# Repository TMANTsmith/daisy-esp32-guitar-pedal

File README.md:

# Daisy Esp32 Pedal

This is a guitar pedal with the goal of combining the audio processing power of the Daisy Seed with the wifi capabilities of the Esp32C series (currently only testing the C6). This way you can fully control the guitar pedal with your phone connected by a website hosted by the esp32 and for low-latency tasks physical buttons will be on the board. This will allow for greater flexibility through the user being able to add or remove buttons by making changes to the website allowing them to have any configuration they want.

## What is used

### Hardware

The mini-pcb which includes TRS jacks for audio processing does not currently have the esp32 but processing audio with just the daisy seed is working

The full-pcb included a esp32 which is connected to the daisy seed through UART (SPI is also connected but is unused) and includes 2 TS jacks this pcb has been designed tested.

#### mini-pcb

- [x] Finished development
- [x] Passed testing

#### full-pcb

|                                 Front                                  |                                 Back                                  |
| :--------------------------------------------------------------------: | :-------------------------------------------------------------------: |
|  |  |

- [x] Finished development
- [x] Passed testing

#### seed-pedal

This will copy the new 3Seed data sheet recommended configuration for instrument level audio and will be the final version

- [ ] Finished development
- [ ] Passed testing

### Software

The project is written in rust and uses embassy as the async executor. Specifically the [daisy-embassy](https://github.com/daisy-embassy/daisy-embassy/tree/master) which has some audio stuff, like a DMA buffer, built in.

## Examples

### Fast-Fourier Transform

- This does a FFT using [microfft](https://gitlab.com/teskje/microfft-rs) but includes things like using the SDRAM on the seed as the heap, interrupts, and how to share information between executor, how to make and use buffer for audio analysis, and more.
- This can show the difference frequencies that a guitar makes when a note it played
- It also has a added mute button

### Looper (work in progress)

- This works like a looper pedal with multiple channels to record different tracks and will be compatible physically so that you can send input to the controller using the website or a physical button
- This uses bit-manipulation to ensure that the commands send and received are compact even if the command library is expanded

## Future Ideas

### Compatibility With Tonebridge

- There are already projects that work with it and all there seems to be is a emulated microphone and speaker which the esp32 may be able to

### Ability to chain custom effects

### More effects

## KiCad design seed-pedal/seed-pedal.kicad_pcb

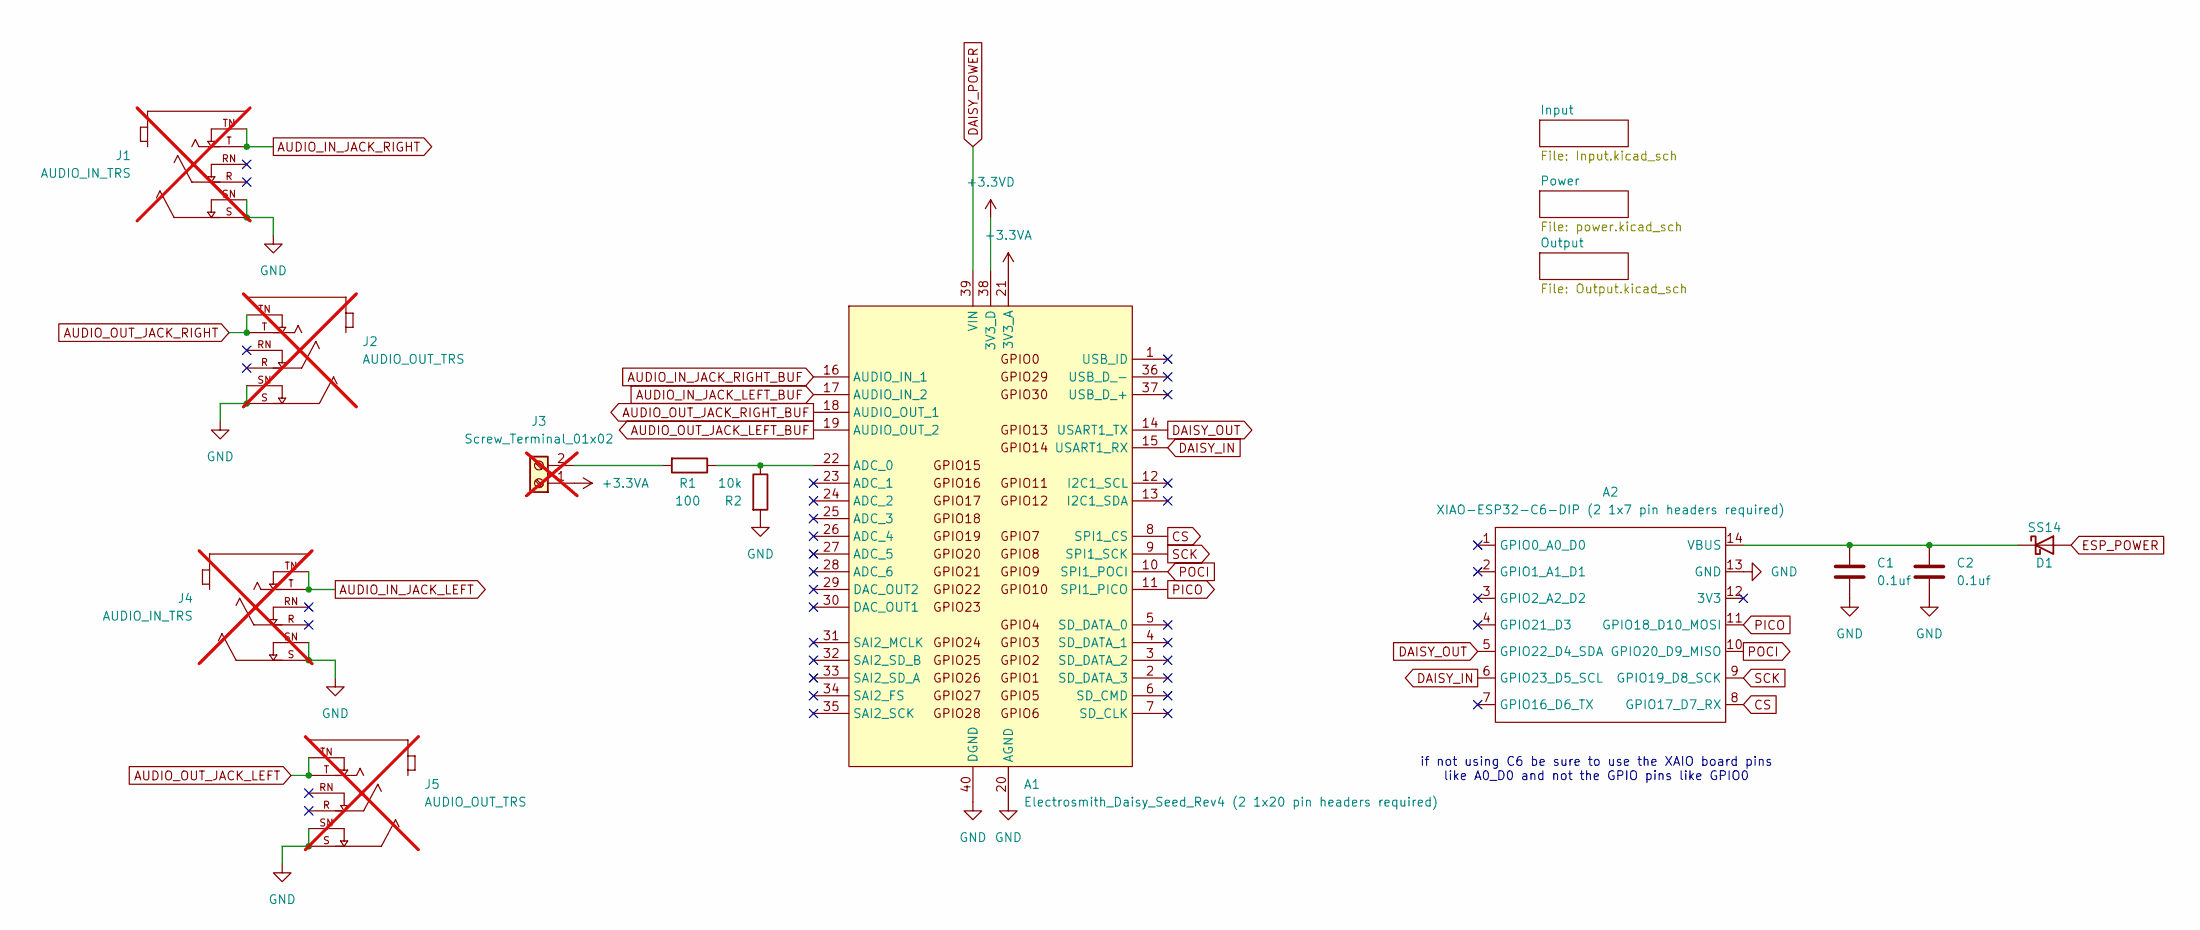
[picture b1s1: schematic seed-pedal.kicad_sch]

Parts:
A1: Electrosmith_Daisy_Seed_Rev4 (2 1x20 pin headers 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; Electrosmith_Daisy_Seed; MPN C50984
A2: XIAO-ESP32-C6-DIP (2 1x7 pin headers required); XIAO-ESP32-C6-DIP; MPN C5371993
C1, C2: 0.1uf; C_0603_1608Metric; MPN C49678
D1: SS14; D_SMA; MPN C2480
J1, J4: AUDIO_IN_TRS; Jack_6.35mm_Neutrik_NMJ6HCD3_Horizontal; PARTREV 26.02.2021; not fitted
J2, J5: AUDIO_OUT_TRS; Jack_6.35mm_Neutrik_NMJ6HCD3_Horizontal; PARTREV 26.02.2021; not fitted
J3: Screw_Terminal_01x02; TerminalBlock_Xinya_XY308-2.54-2P_1x02_P2.54mm_Horizontal; MPN C8465; not fitted
R1: 100; R_0603_1608Metric; MPN C22775
R2: 10k; R_0603_1608Metric; MPN C25804

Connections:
+3.3VA: A1.21 (3V3_A), J3.1
+3.3VD: A1.38 (3V3_D)
AUDIO_IN_JACK_LEFT: J4.T, J4.TN; also elsewhere on the board
AUDIO_IN_JACK_LEFT_BUF: A1.17 (AUDIO_IN_2); also elsewhere on the board
AUDIO_IN_JACK_RIGHT: J1.T, J1.TN; also elsewhere on the board
AUDIO_IN_JACK_RIGHT_BUF: A1.16 (AUDIO_IN_1); also elsewhere on the board
AUDIO_OUT_JACK_LEFT: J5.T, J5.TN; also elsewhere on the board
AUDIO_OUT_JACK_LEFT_BUF: A1.19 (AUDIO_OUT_2); also elsewhere on the board
AUDIO_OUT_JACK_RIGHT: J2.T, J2.TN; also elsewhere on the board
AUDIO_OUT_JACK_RIGHT_BUF: A1.18 (AUDIO_OUT_1); also elsewhere on the board
CS: A1.8 (SPI1_CS), A2.8 (GPIO17_D7_RX)
DAISY_IN: A1.15 (USART1_RX), A2.6 (GPIO23_D5_SCL)
DAISY_OUT: A1.14 (USART1_TX), A2.5 (GPIO22_D4_SDA)
DAISY_POWER: A1.39 (VIN); also elsewhere on the board
ESP_POWER: D1.2 (A); also elsewhere on the board
GND: A1.20 (AGND), A1.40 (DGND), A2.13 (GND), C1.2, C2.2, J1.S, J1.SN, J2.S, J2.SN, J4.S, J4.SN, J5.S, J5.SN, R2.2; also elsewhere on the board
unnamed: A1.22 (ADC_0), R1.1, R2.1
unnamed: A2.14 (VBUS), C1.1, C2.1, D1.1 (K)
unnamed: J3.2, R1.2
PICO: A1.11 (SPI1_PICO), A2.11 (GPIO18_D10_MOSI)
POCI: A1.10 (SPI1_POCI), A2.10 (GPIO20_D9_MISO)
SCK: A1.9 (SPI1_SCK), A2.9 (GPIO19_D8_SCK)

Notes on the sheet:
if not using C6 be sure to use the XAIO board pins like A0_D0 and not the GPIO pins like GPIO0

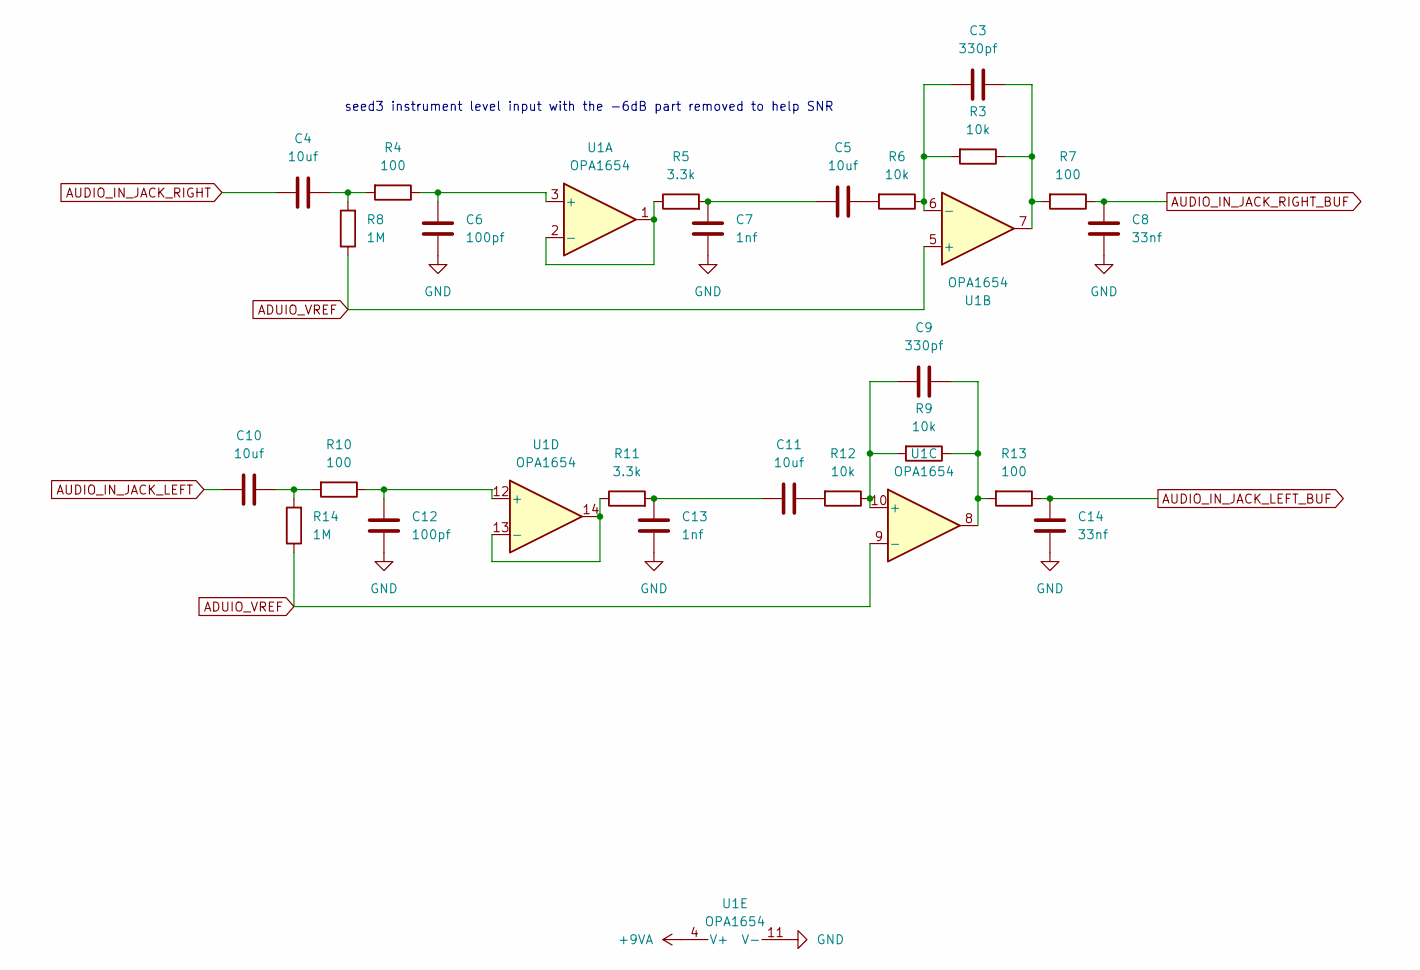
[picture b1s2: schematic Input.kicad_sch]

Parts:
C3, C9: 330pf; C_0603_1608Metric; MPN C1664
C4, C5, C10, C11: 10uf; C_0603_1608Metric; MPN C96446
C6, C12: 100pf; C_0603_1608Metric; MPN C14858
C7, C13: 1nf; C_0603_1608Metric; MPN C1588
C8, C14: 33nf; C_0603_1608Metric; MPN C21117
R3, R6, R9, R12: 10k; R_0603_1608Metric; MPN C25804
R4, R7, R10, R13: 100; R_0603_1608Metric; MPN C22775
R5, R11: 3.3k; R_0603_1608Metric; MPN C22978
R8, R14: 1M; R_0603_1608Metric; MPN C22935
U1: OPA1654; SOIC-14_3.9x8.7mm_P1.27mm; MPN C30026

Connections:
+9VA: U1.4 (V+); also elsewhere on the board
ADUIO_VREF: R8.1, R14.1, U1.5 (+), U1.9 (-); also elsewhere on the board
AUDIO_IN_JACK_LEFT: C10.1; also elsewhere on the board
AUDIO_IN_JACK_LEFT_BUF: C14.1, R13.1; also elsewhere on the board
AUDIO_IN_JACK_RIGHT: C4.1; also elsewhere on the board
AUDIO_IN_JACK_RIGHT_BUF: C8.1, R7.1; also elsewhere on the board
GND: C6.2, C7.2, C8.2, C12.2, C13.2, C14.2, U1.11 (V-); also elsewhere on the board
unnamed: C3.2, R3.1, R7.2, U1.7
unnamed: C4.2, R4.2, R8.2
unnamed: C5.1, C7.1, R5.2
unnamed: C5.2, R6.2
unnamed: C9.2, R9.1, R13.2, U1.8
unnamed: C10.2, R10.2, R14.2
unnamed: C11.1, C13.1, R11.2
unnamed: C11.2, R12.2
unnamed: C6.1, R4.1, U1.3 (+)
unnamed: R5.1, U1.1, U1.2 (-)
unnamed: C3.1, R3.2, R6.1, U1.6 (-)
unnamed: C9.1, R9.2, R12.1, U1.10 (+)
unnamed: C12.1, R10.1, U1.12 (+)
unnamed: R11.1, U1.13 (-), U1.14

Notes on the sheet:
seed3 instrument level input with the -6dB part removed to help SNR

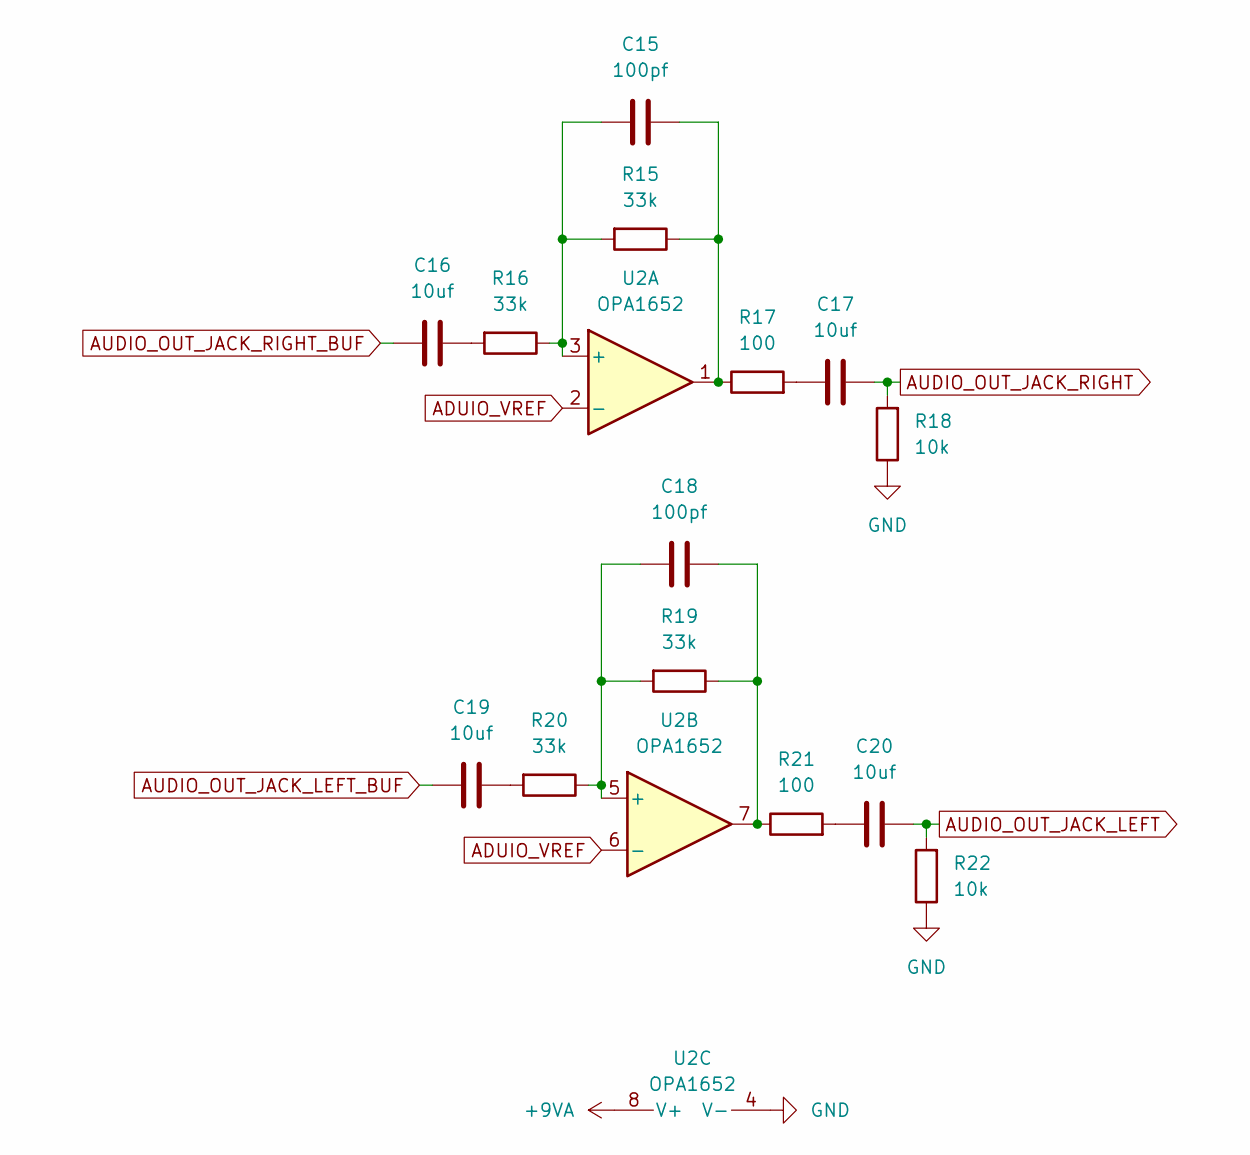
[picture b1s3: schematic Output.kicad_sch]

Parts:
C15, C18: 100pf; C_0603_1608Metric; MPN C14858
C16, C17, C19, C20: 10uf; C_0603_1608Metric; MPN C96446
R15, R16, R19, R20: 33k; R_0603_1608Metric; MPN C4216
R17, R21: 100; R_0603_1608Metric; MPN C22775
R18, R22: 10k; R_0603_1608Metric; MPN C25804
U2: OPA1652; SOIC-8_3.9x4.9mm_P1.27mm

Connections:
+9VA: U2.8 (V+); also elsewhere on the board
ADUIO_VREF: U2.2 (-), U2.6 (-); also elsewhere on the board
AUDIO_OUT_JACK_LEFT: C20.2, R22.2; also elsewhere on the board
AUDIO_OUT_JACK_LEFT_BUF: C19.1; also elsewhere on the board
AUDIO_OUT_JACK_RIGHT: C17.2, R18.2; also elsewhere on the board
AUDIO_OUT_JACK_RIGHT_BUF: C16.1; also elsewhere on the board
GND: R18.1, R22.1, U2.4 (V-); also elsewhere on the board
unnamed: C15.2, R15.1, R17.1, U2.1
unnamed: C16.2, R16.2
unnamed: C17.1, R17.2
unnamed: C18.2, R19.1, R21.1, U2.7
unnamed: C19.2, R20.2
unnamed: C20.1, R21.2
unnamed: C15.1, R15.2, R16.1, U2.3 (+)
unnamed: C18.1, R19.2, R20.1, U2.5 (+)

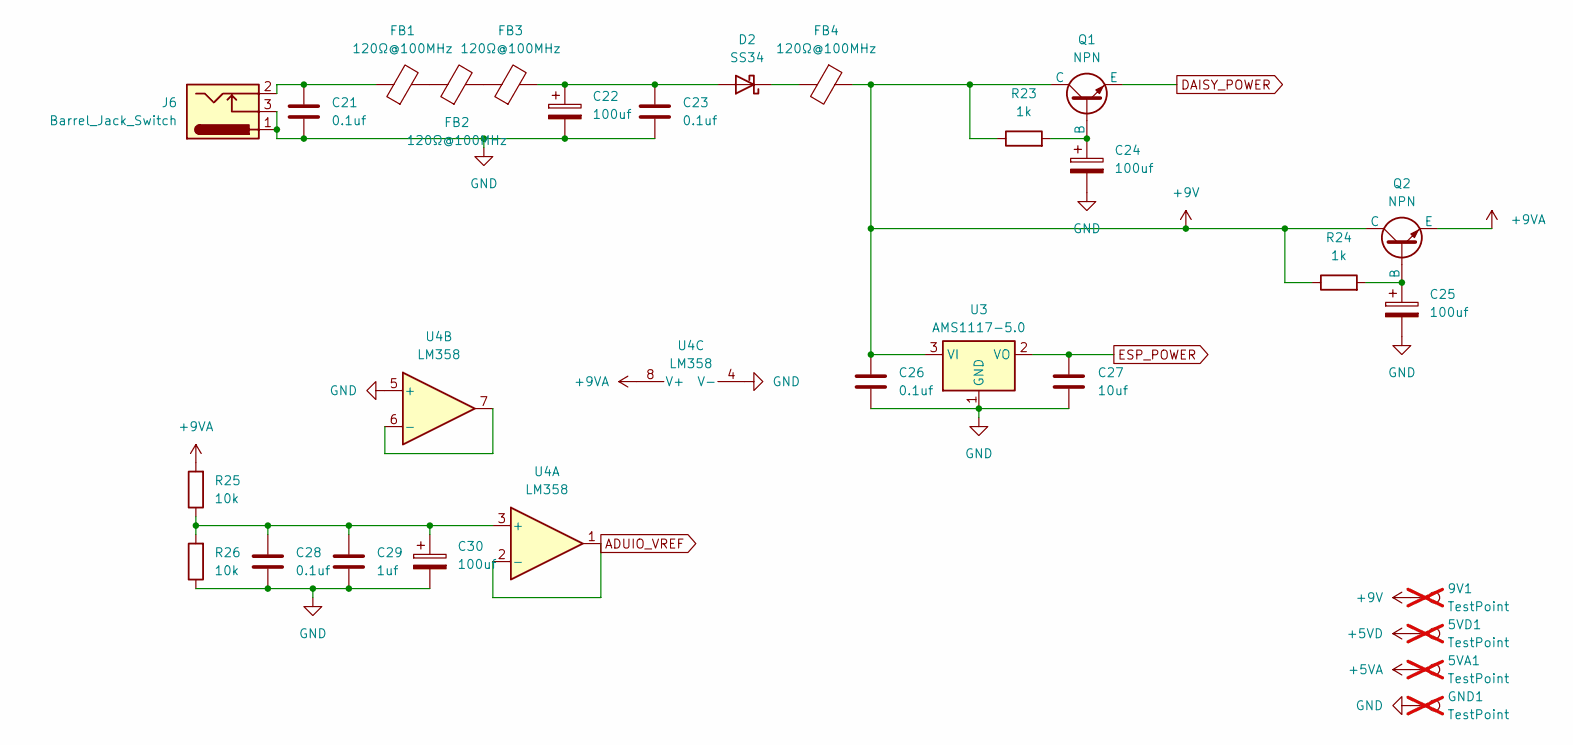
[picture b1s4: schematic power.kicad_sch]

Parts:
5VA1, 5VD1, 9V1: TestPoint; PinHeader_1x01_P2.54mm_Vertical; not fitted
C21, C23, C26, C28: 0.1uf; C_0805_2012Metric; MPN C49678
C22, C24, C25, C30: 100uf; CP_Radial_D8.0mm_P3.50mm; MPN C5113358
C27: 10uf; C_0805_2012Metric; MPN C15850
C29: 1uf; C_0805_2012Metric; MPN C28323
D2: SS34; D_SMA
FB1, FB2, FB3, FB4: 120Ω@100MHz; R_0603_1608Metric; MPN BLM18PG121SN1D
GND1: TestPoint; PinHeader_1x01_P2.54mm_Vertical; not fitted
J6: Barrel_Jack_Switch; BarrelJack_Horizontal; MPN C16214
Q1, Q2: NPN; SOT-89-3; MPN C41375136
R23, R24: 1k; R_0603_1608Metric; MPN C21190
R25, R26: 10k; R_0603_1608Metric; MPN C25804
U3: AMS1117-5.0; SOT-223-3_TabPin2
U4: LM358; SOIC-8_3.9x4.9mm_P1.27mm

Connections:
+9V: 9V1.1, C26.1, FB4.1, Q1.1 (C), Q2.1 (C), R23.1, R24.1, U3.3 (VI)
+9VA: Q2.3 (E), R25.2, U4.8 (V+); also elsewhere on the board
ADUIO_VREF: U4.1, U4.2 (-); also elsewhere on the board
DAISY_POWER: Q1.3 (E); also elsewhere on the board
ESP_POWER: C27.2, U3.2 (VO); also elsewhere on the board
GND: C21.2, C22.2, C23.2, C24.2, C25.2, C26.2, C27.1, C28.2, C29.2, C30.2, GND1.1 (1_1), J6.1, J6.3, R26.1, U3.1 (GND), U4.4 (V-), U4.5 (+); also elsewhere on the board
unnamed: C21.1, FB1.1, J6.2
unnamed: C22.1, C23.1, D2.2 (A), FB3.2
unnamed: D2.1 (K), FB4.2
unnamed: FB1.2, FB2.1
unnamed: FB2.2, FB3.1
unnamed: C24.1, Q1.2 (B), R23.2
unnamed: C25.1, Q2.2 (B), R24.2
unnamed: C28.1, C29.1, C30.1, R25.1, R26.2, U4.3 (+)
unnamed: U4.6 (-), U4.7

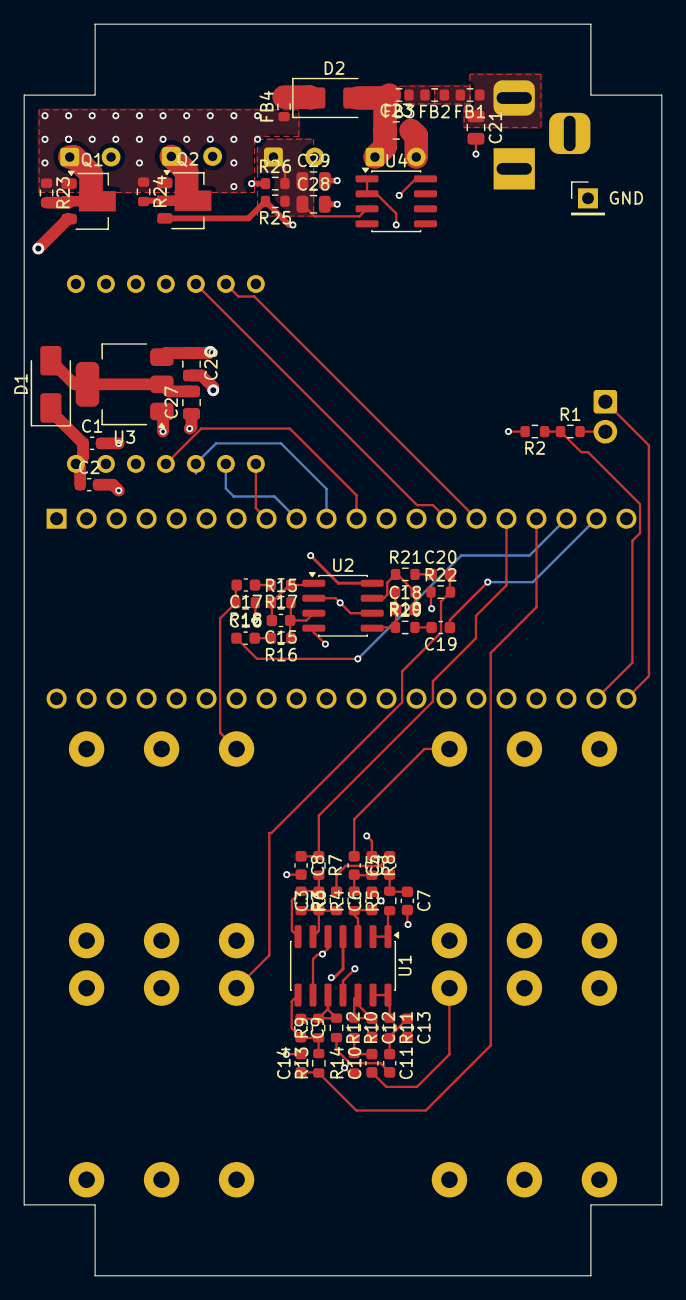
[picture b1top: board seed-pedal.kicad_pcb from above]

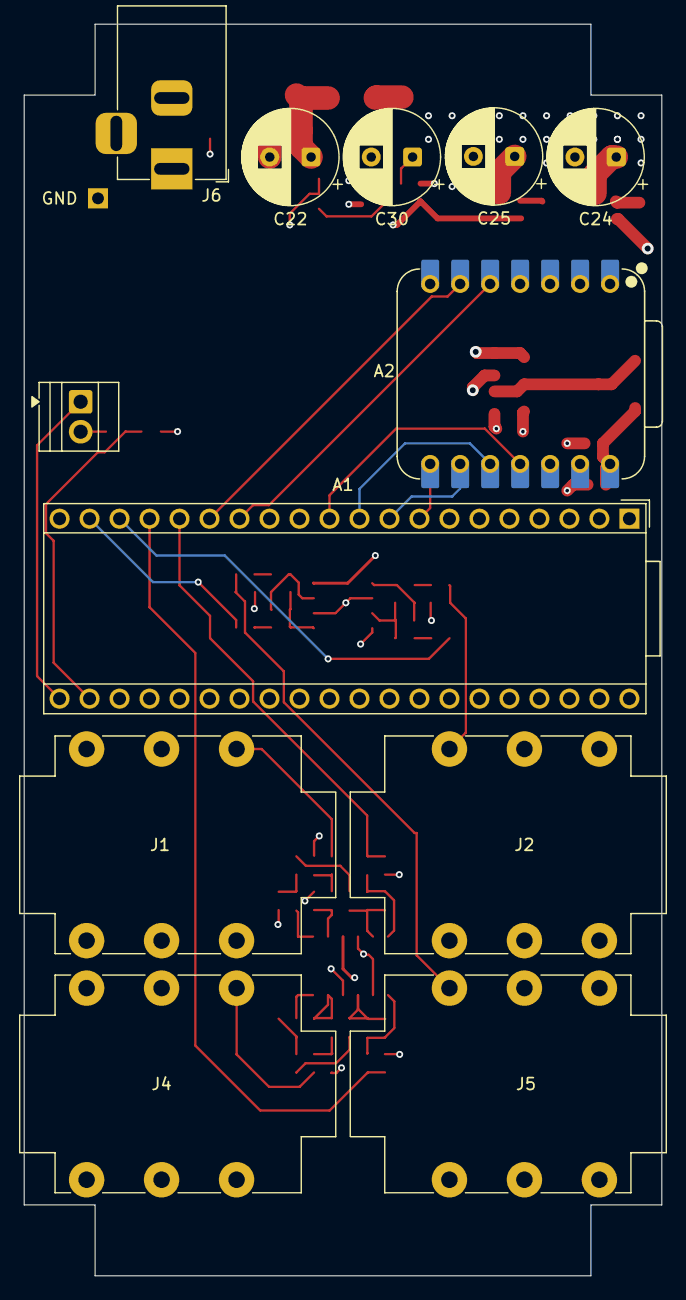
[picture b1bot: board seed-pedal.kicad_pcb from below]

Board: 4 copper layers, 54.0 x 106.0 mm, 77 parts (12 on the bottom side), 55 nets.

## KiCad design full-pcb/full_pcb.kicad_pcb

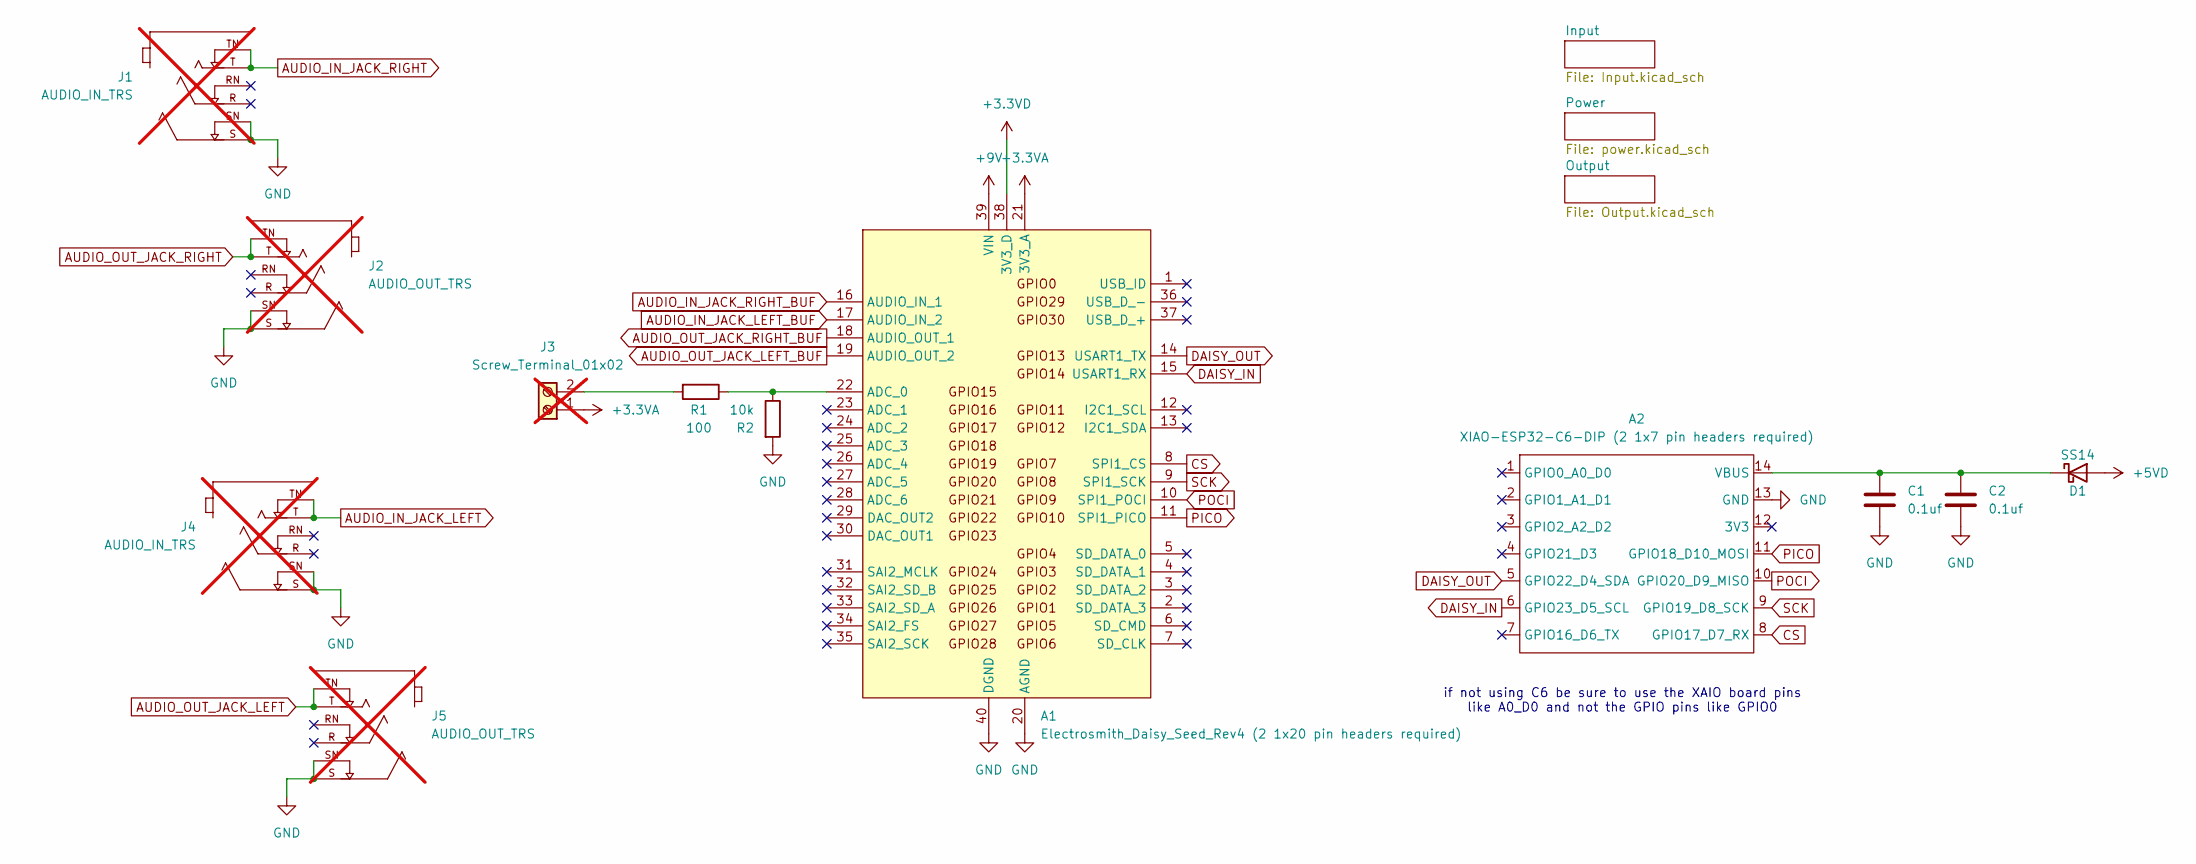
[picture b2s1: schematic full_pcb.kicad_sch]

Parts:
A1: Electrosmith_Daisy_Seed_Rev4 (2 1x20 pin headers 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; Electrosmith_Daisy_Seed; MPN C50984
A2: XIAO-ESP32-C6-DIP (2 1x7 pin headers required); XIAO-ESP32-C6-DIP; MPN C5371993
C1, C2: 0.1uf; C_0805_2012Metric; MPN C49678
D1: SS14; D_SMA; MPN C2480
J1, J4: AUDIO_IN_TRS; Jack_6.35mm_Neutrik_NMJ6HCD3_Horizontal; PARTREV 26.02.2021; not fitted
J2, J5: AUDIO_OUT_TRS; Jack_6.35mm_Neutrik_NMJ6HCD3_Horizontal; PARTREV 26.02.2021; not fitted
J3: Screw_Terminal_01x02; TerminalBlock_Xinya_XY308-2.54-2P_1x02_P2.54mm_Horizontal; MPN C8465; not fitted
R1: 100; R_0603_1608Metric; MPN C22775
R2: 10k; R_0603_1608Metric; MPN C25804

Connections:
+3.3VA: A1.21 (3V3_A), J3.1
+3.3VD: A1.38 (3V3_D)
+5VD: D1.2 (A); also elsewhere on the board
+9V: A1.39 (VIN); also elsewhere on the board
AUDIO_IN_JACK_LEFT: J4.T, J4.TN; also elsewhere on the board
AUDIO_IN_JACK_LEFT_BUF: A1.17 (AUDIO_IN_2); also elsewhere on the board
AUDIO_IN_JACK_RIGHT: J1.T, J1.TN; also elsewhere on the board
AUDIO_IN_JACK_RIGHT_BUF: A1.16 (AUDIO_IN_1); also elsewhere on the board
AUDIO_OUT_JACK_LEFT: J5.T, J5.TN; also elsewhere on the board
AUDIO_OUT_JACK_LEFT_BUF: A1.19 (AUDIO_OUT_2); also elsewhere on the board
AUDIO_OUT_JACK_RIGHT: J2.T, J2.TN; also elsewhere on the board
AUDIO_OUT_JACK_RIGHT_BUF: A1.18 (AUDIO_OUT_1); also elsewhere on the board
CS: A1.8 (SPI1_CS), A2.8 (GPIO17_D7_RX)
DAISY_IN: A1.15 (USART1_RX), A2.6 (GPIO23_D5_SCL)
DAISY_OUT: A1.14 (USART1_TX), A2.5 (GPIO22_D4_SDA)
GND: A1.20 (AGND), A1.40 (DGND), A2.13 (GND), C1.2, C2.2, J1.S, J1.SN, J2.S, J2.SN, J4.S, J4.SN, J5.S, J5.SN, R2.2; also elsewhere on the board
unnamed: A1.22 (ADC_0), R1.1, R2.1
unnamed: A2.14 (VBUS), C1.1, C2.1, D1.1 (K)
unnamed: J3.2, R1.2
PICO: A1.11 (SPI1_PICO), A2.11 (GPIO18_D10_MOSI)
POCI: A1.10 (SPI1_POCI), A2.10 (GPIO20_D9_MISO)
SCK: A1.9 (SPI1_SCK), A2.9 (GPIO19_D8_SCK)

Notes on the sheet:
if not using C6 be sure to use the XAIO board pins like A0_D0 and not the GPIO pins like GPIO0

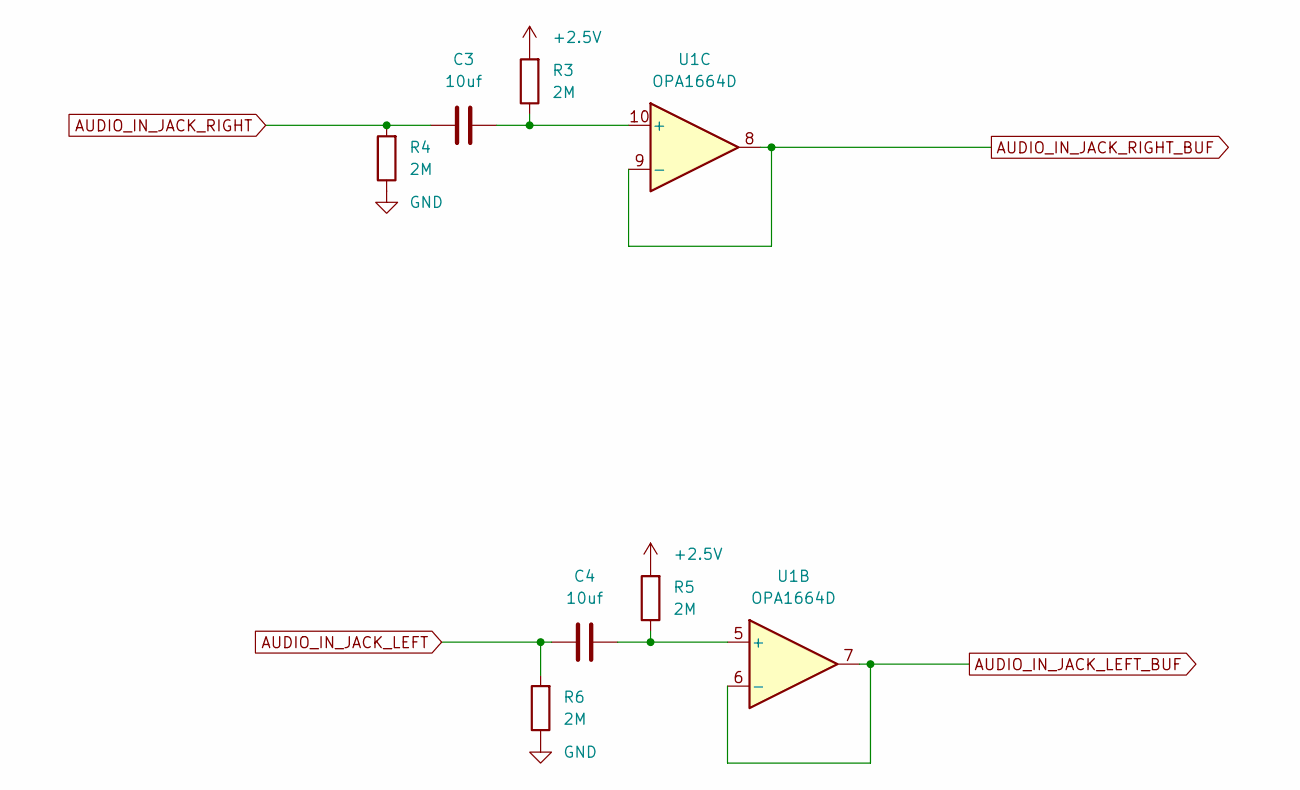
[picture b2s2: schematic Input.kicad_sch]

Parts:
C3, C4: 10uf; C_0805_2012Metric; MPN C440198
R3, R4, R5, R6: 2M; R_0603_1608Metric; MPN C22976
U1: OPA1664D; SOIC-14_3.9x8.7mm_P1.27mm; MPN C69414

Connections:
+2.5V: R3.2, R5.2; also elsewhere on the board
AUDIO_IN_JACK_LEFT: C4.1, R6.2; also elsewhere on the board
AUDIO_IN_JACK_LEFT_BUF: U1.6 (-), U1.7; also elsewhere on the board
AUDIO_IN_JACK_RIGHT: C3.1, R4.2; also elsewhere on the board
AUDIO_IN_JACK_RIGHT_BUF: U1.8, U1.9 (-); also elsewhere on the board
GND: R4.1, R6.1; also elsewhere on the board
unnamed: C4.2, R5.1, U1.5 (+)
unnamed: C3.2, R3.1, U1.10 (+)

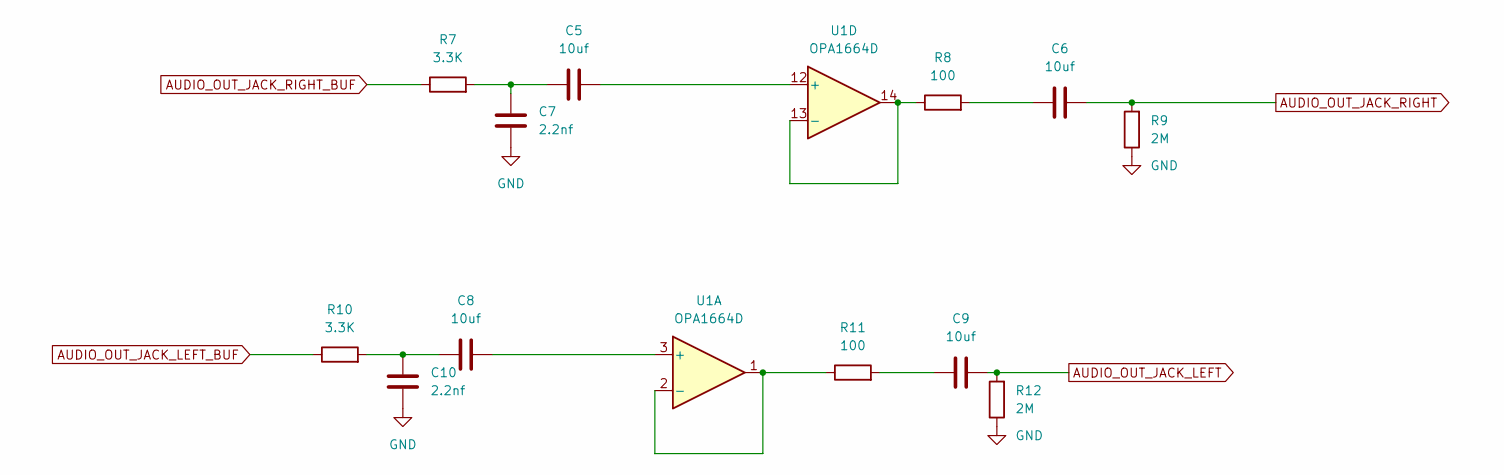
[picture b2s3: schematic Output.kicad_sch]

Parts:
C5, C6, C8, C9: 10uf; C_0805_2012Metric; MPN C440198
C7, C10: 2.2nf; C_0805_2012Metric; MPN C28260
R7, R10: 3.3K; R_0603_1608Metric; MPN C22978
R8, R11: 100; R_0603_1608Metric; MPN C22775
R9, R12: 2M; R_0603_1608Metric; MPN C22976
U1: OPA1664D; SOIC-14_3.9x8.7mm_P1.27mm; MPN C69414

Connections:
AUDIO_OUT_JACK_LEFT: C9.2, R12.2; also elsewhere on the board
AUDIO_OUT_JACK_LEFT_BUF: R10.1; also elsewhere on the board
AUDIO_OUT_JACK_RIGHT: C6.2, R9.2; also elsewhere on the board
AUDIO_OUT_JACK_RIGHT_BUF: R7.1; also elsewhere on the board
GND: C7.1, C10.1, R9.1, R12.1; also elsewhere on the board
unnamed: C5.1, C7.2, R7.2
unnamed: C6.1, R8.2
unnamed: C9.1, R11.2
unnamed: C8.1, C10.2, R10.2
unnamed: C8.2, U1.3 (+)
unnamed: R11.1, U1.1, U1.2 (-)
unnamed: C5.2, U1.12 (+)
unnamed: R8.1, U1.13 (-), U1.14

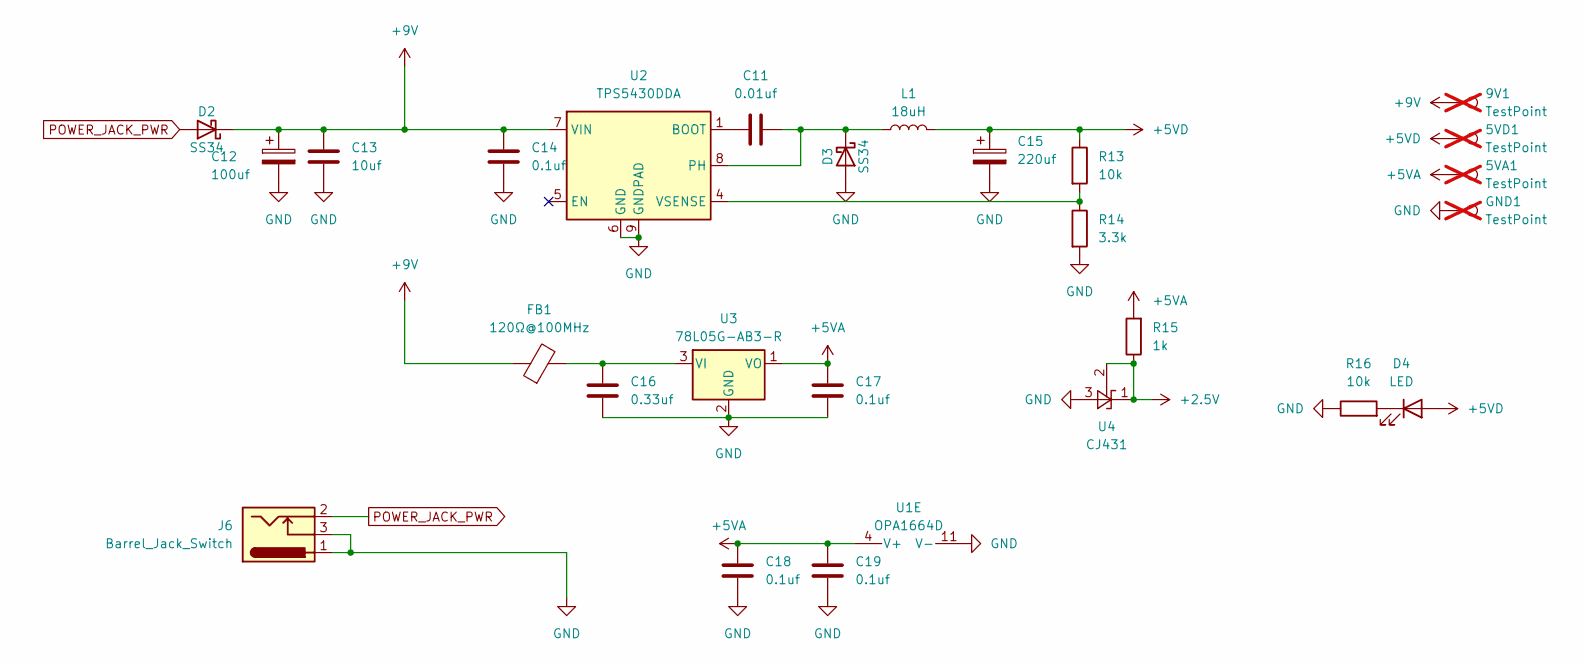
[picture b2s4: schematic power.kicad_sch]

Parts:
5VA1, 5VD1, 9V1: TestPoint; PinHeader_1x01_P2.54mm_Vertical; not fitted
C11: 0.01uf; C_0805_2012Metric; MPN C1710
C12: 100uf; CP_EIA-3528-21_Kemet-B; MPN C16133
C13: 10uf; C_0805_2012Metric; MPN C440198
C14, C17, C18, C19: 0.1uf; C_0805_2012Metric; MPN C49678
C15: 220uf; CP_EIA-7343-31_Kemet-D; MPN C242173
C16: 0.33uf; C_0805_2012Metric; MPN C1740
D2, D3: SS34; D_SMA; MPN C8678
D4: LED; LED_0805_2012Metric; MPN C2297
FB1: 120Ω@100MHz; R_0603_1608Metric; MPN C14709
GND1: TestPoint; PinHeader_1x01_P2.54mm_Vertical; not fitted
J6: Barrel_Jack_Switch; BarrelJack_Horizontal; MPN C16214
L1: 18uH; L_Changjiang_FNR8040S; MPN C168130
R13, R16: 10k; R_0603_1608Metric; MPN C25804
R14: 3.3k; R_0603_1608Metric; MPN C22978
R15: 1k; R_0603_1608Metric; MPN C21190
U1: OPA1664D; SOIC-14_3.9x8.7mm_P1.27mm; MPN C69414
U2: TPS5430DDA; TI_SO-PowerPAD-8_ThermalVias; MPN C9864
U3: 78L05G-AB3-R; SOT-89-3; MPN C71136
U4: CJ431; SOT-23-3; MPN C3113

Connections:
+2.5V: R15.1, U4.1 (FB), U4.2 (K); also elsewhere on the board
+5VA: 5VA1.1 (1_1), C17.2, C18.1, C19.1, R15.2, U1.4 (V+), U3.1 (VO)
+5VD: 5VD1.1 (1_1), C15.1, D4.2 (A), L1.2, R13.1; also elsewhere on the board
+9V: 9V1.1 (1_1), C12.1, C13.2, C14.2, D2.1 (K), FB1.1, U2.7 (VIN); also elsewhere on the board
GND: C12.2, C13.1, C14.1, C15.2, C16.1, C17.1, C18.2, C19.2, D3.2 (A), GND1.1 (1_1), J6.1, J6.3, R14.2, R16.1, U1.11 (V-), U2.6 (GND), U2.9 (GNDPAD), U3.2 (GND), U4.3 (A); also elsewhere on the board
unnamed: C11.2, D3.1 (K), L1.1, U2.8 (PH)
unnamed: D4.1 (K), R16.2
unnamed: C11.1, U2.1 (BOOT)
unnamed: R13.2, R14.1, U2.4 (VSENSE)
unnamed: C16.2, FB1.2, U3.3 (VI)
POWER_JACK_PWR: D2.2 (A), J6.2

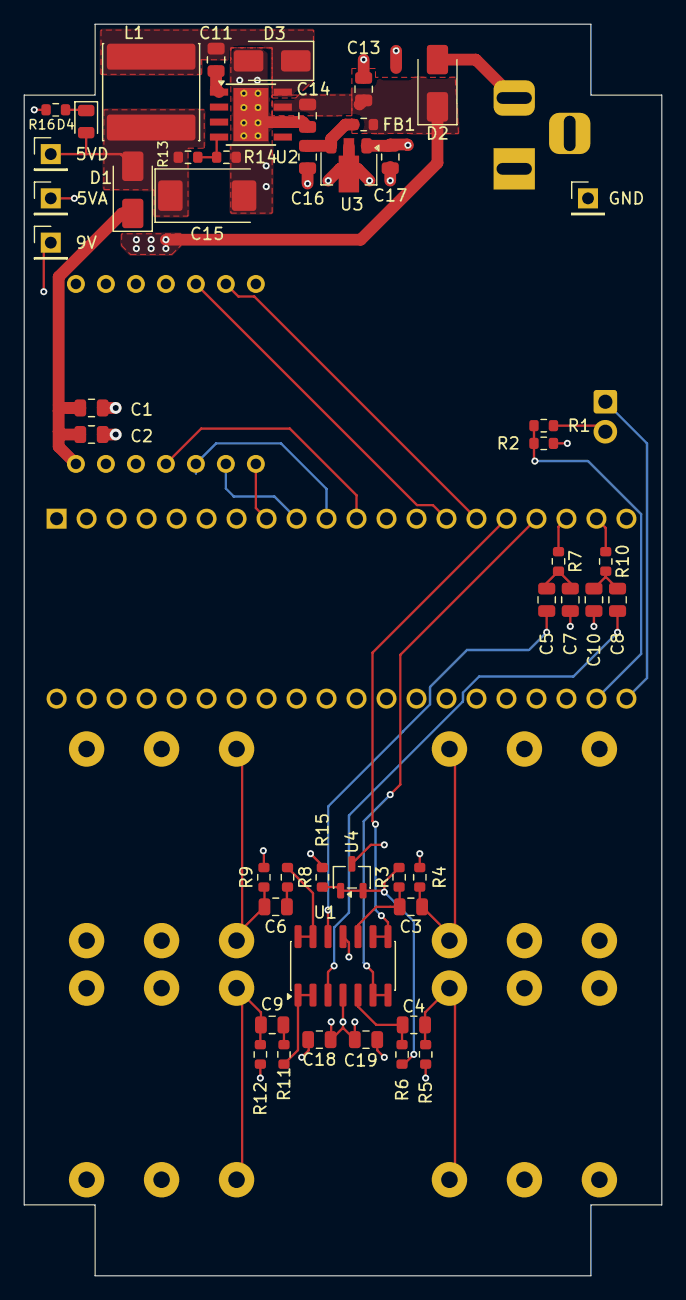
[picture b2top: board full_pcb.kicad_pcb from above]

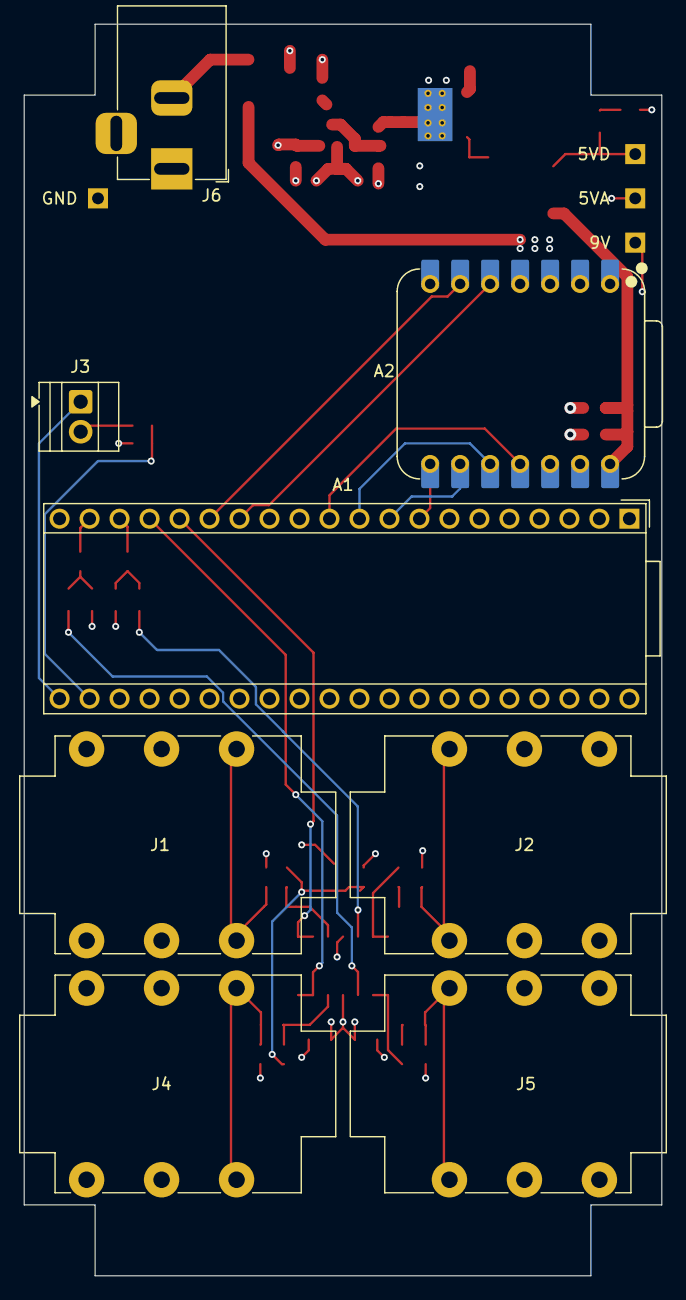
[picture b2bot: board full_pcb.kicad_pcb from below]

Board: 4 copper layers, 54.0 x 106.0 mm, 56 parts (8 on the bottom side), 39 nets.

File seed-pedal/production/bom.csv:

Designator,Footprint,Quantity,Value,LCSC Part #
"5VA1, 5VD1, 9V1, GND1",PinHeader_1x01_P2.54mm_Vertical,4,TestPoint,
A1,Electrosmith_Daisy_Seed,1,Electrosmith_Daisy_Seed_Rev4 (2 1x20 pin headers required),C50984
A2,XIAO-ESP32-C6-DIP,1,XIAO-ESP32-C6-DIP  (2 1x7 pin headers required),C5371993
"C1, C14, C17, C18, C19, C2",0805,6,0.1uf,C49678
"C10, C7",0805,2,2.2nf,C28260
C11,0805,1,0.01uf,C1710
C12,CP_EIA-3528-21_Kemet-B,1,100uf,C16133
"C13, C3, C4, C5, C6, C8, C9",0805,7,10uf,C440198
C15,CP_EIA-7343-31_Kemet-D,1,220uf,C242173
C16,0805,1,0.33uf,C1740
D1,D_SMA,1,SS14,C2480
"D2, D3",D_SMA,2,SS34,C8678
D4,0805,1,LED,C2297
FB1,0603,1,120Ω@100MHz,C14709
J6,BarrelJack_Horizontal,1,Barrel_Jack_Switch,C16214
L1,L_Changjiang_FNR8040S,1,18uH,C168130
"R1, R11, R8",0603,3,100,C22775
"R10, R14, R7",0603,3,3.3K,C22978
"R12, R3, R4, R5, R6, R9",0603,6,2M,C22976
"R13, R16, R2",0603,3,10k,C25804
R15,0603,1,1k,C21190
U1,SOIC-14_3.9x8.7mm_P1.27mm,1,OPA1664D,C69414
U2,TI_SO-PowerPAD-8_ThermalVias,1,TPS5430DDA,C9864
U3,SOT-89-3,1,78L05G-AB3-R,C71136
U4,SOT-23-3,1,CJ431,C3113
